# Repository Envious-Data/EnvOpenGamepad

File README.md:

# EnvOpenGamepad
 An open source gamepad using a RP2040 designed to be like popular gamepads but with a few bonus features and ease of repairability.

## Planned features
- layout similar to popular models
- additional buttons over popular models
- turbo mode
- hall effect sticks and triggers

## Features I want but cant implement (yet?)
- vibration/rumble
- wireless
- touchpad?

## Why

no real reason, I had this idea bouncing around in my head for ages so to procrastinate on other projects ill work on this one till I procrastinate on this one by working on others but really I just enjoy designing and making things and if they serve as a good example to do something whilst also helping me learn then its doing one of its main jobs.

I generally like things that can be repaired so if I can make something that surpasses a commercially avaliable example while being reasonable in cost then thats great because I really dont like not being able to repair things which is sometimes the case for commercially avaliable solutions.

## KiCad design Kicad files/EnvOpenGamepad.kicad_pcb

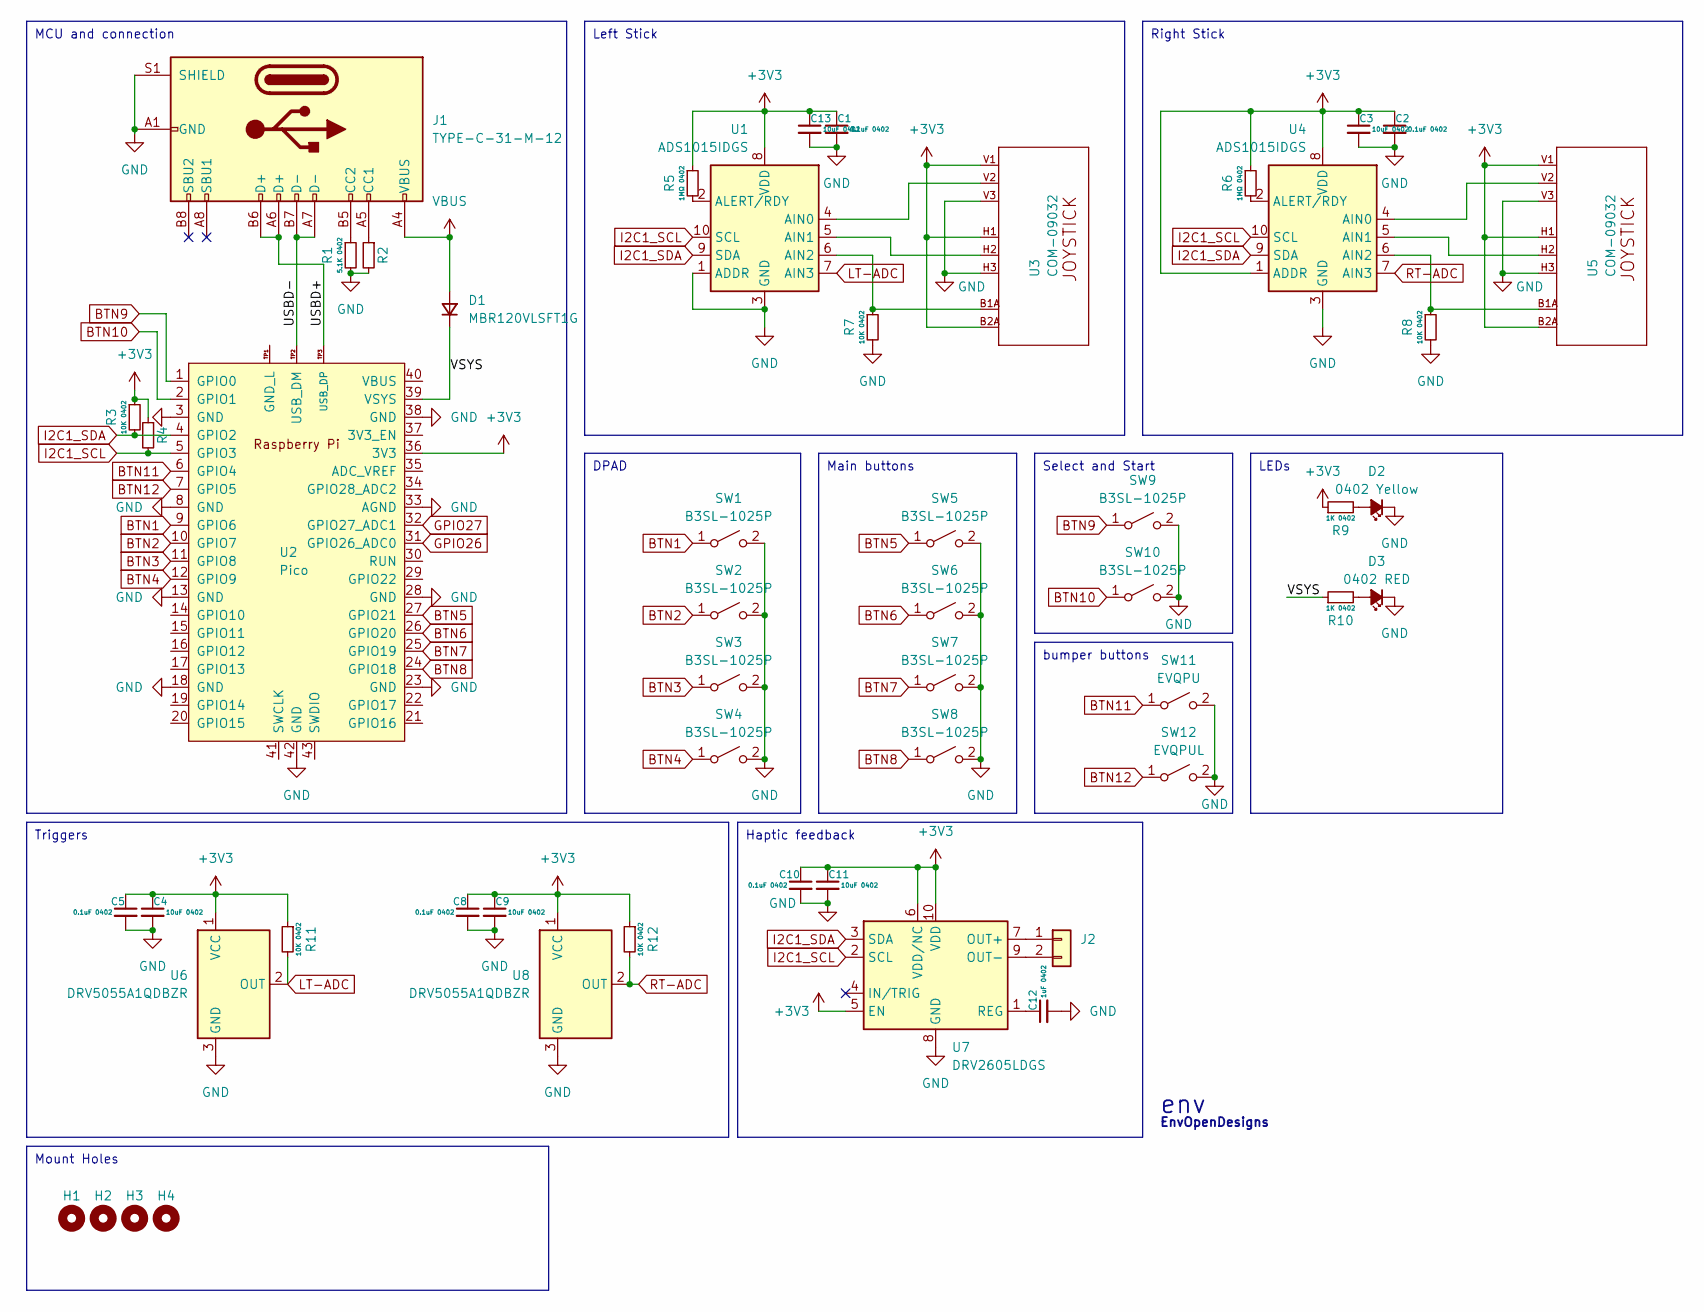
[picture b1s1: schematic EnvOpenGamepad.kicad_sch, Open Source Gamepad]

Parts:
C1, C2, C5, C8, C10: 0.1uF 0402; C_0402_1005Metric
C3, C4, C9, C11, C13: 10uF 0402; C_0402_1005Metric
C12: 1uF 0402; C_0402_1005Metric
D1: MBR120VLSFT1G; D_SOD-123F
D2: 0402 Yellow; LED_0402_1005Metric
D3: 0402 RED; LED_0402_1005Metric
H1, H2, H3, H4: M2 Mounting Hole; MountingHole_2.2mm_M2
J1: TYPE-C-31-M-12; USB_C_Receptacle_HRO_TYPE-C-31-M-12
J2: 01x02 2.54mm pin header; PinHeader_1x02_P2.54mm_Vertical
R1, R2, R4: 5.1K 0402; R_0402_1005Metric
R3, R7, R8, R11, R12: 10K 0402; R_0402_1005Metric
R5, R6: 1MΩ 0402; R_0402_1005Metric
R9, R10: 1K 0402; R_0402_1005Metric
SW1, SW2, SW3, SW4, SW5, SW6, SW7, SW8, SW9, SW10: B3SL-1025P; SW_SPST_B3SL-1022P
SW11: EVQPU; Panasonic_EVQPUL_EVQPUC
SW12: EVQPUL; Panasonic_EVQPUL_EVQPUC
U1, U4: ADS1015IDGS; TSSOP-10_3x3mm_P0.5mm
U2: Pico; RPi_Pico_SMD_TH
U3, U5: COM-09032; JOYSTICK
U6, U8: DRV5055A1QDBZR; SOT-23
U7: DRV2605LDGS; VSSOP-10_3x3mm_P0.5mm

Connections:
+3V3: C1.1, C2.1, C3.1, C4.1, C5.1, C8.1, C9.1, C10.1, C11.1, C13.1, R3.1, R4.1, R5.1, R6.1, R9.1, R11.1, R12.1, U1.8 (VDD), U2.36 (3V3), U3.B2A (SEL-), U3.H1 (H+), U3.V1 (V+), U4.1 (ADDR), U4.8 (VDD), U5.B2A (SEL-), U5.H1 (H+), U5.V1 (V+), U6.1 (VCC), U7.5 (EN), U7.6 (VDD/NC), U7.10 (VDD), U8.1 (VCC)
/USBD+: J1.A6 (D+), J1.B6 (D+), U2.TP3 (USB_DP)
/USBD-: J1.A7 (D-), J1.B7 (D-), U2.TP2 (USB_DM)
/VSYS: D1.1 (K), R10.1, U2.39 (VSYS)
BTN1: SW1.1 (A), U2.9 (GPIO6)
BTN2: SW2.1 (A), U2.10 (GPIO7)
BTN3: SW3.1 (A), U2.11 (GPIO8)
BTN4: SW4.1 (A), U2.12 (GPIO9)
BTN5: SW5.1 (A), U2.27 (GPIO21)
BTN6: SW6.1 (A), U2.26 (GPIO20)
BTN7: SW7.1 (A), U2.25 (GPIO19)
BTN8: SW8.1 (A), U2.24 (GPIO18)
BTN9: SW9.1 (A), U2.1 (GPIO0)
BTN10: SW10.1 (A), U2.2 (GPIO1)
BTN11: SW11.1 (A), U2.6 (GPIO4)
BTN12: SW12.1 (A), U2.7 (GPIO5)
GND: C1.2, C2.2, C3.2, C4.2, C5.2, C8.2, C9.2, C10.2, C11.2, C12.2, C13.2, D2.1 (K), D3.1 (K), J1.A1 (GND), J1.A12 (GND), J1.B1 (GND), J1.B12 (GND), J1.S1 (SHIELD), R1.2, R2.2, R7.2, R8.2, SW1.2 (B), SW2.2 (B), SW3.2 (B), SW4.2 (B), SW5.2 (B), SW6.2 (B), SW7.2 (B), SW8.2 (B), SW9.2 (B), SW10.2 (B), SW11.2 (B), SW12.2 (B), U1.1 (ADDR), U1.3 (GND), U2.3 (GND), U2.8 (GND), U2.13 (GND), U2.18 (GND), U2.23 (GND), U2.28 (GND), U2.33 (AGND), U2.38 (GND), U2.42 (GND), U3.H3 (H-), U3.V3 (V-), U4.3 (GND), U5.H3 (H-), U5.V3 (V-), U6.3 (GND), U7.8 (GND), U8.3 (GND)
GPIO26: U2.31 (GPIO26_ADC0)
GPIO27: U2.32 (GPIO27_ADC1)
I2C1_SCL: R4.2, U1.10 (SCL), U2.5 (GPIO3), U4.10 (SCL), U7.2 (SCL)
I2C1_SDA: R3.2, U1.9 (SDA), U2.4 (GPIO2), U4.9 (SDA), U7.3 (SDA)
LT-ADC: R11.2, U1.7 (AIN3), U6.2 (OUT)
unnamed: D2.2 (A), R9.2
unnamed: D3.2 (A), R10.2
unnamed: J1.A5 (CC1), R2.1
unnamed: J1.B5 (CC2), R1.1
unnamed: J2.1, U7.7 (OUT+)
unnamed: J2.2, U7.9 (OUT-)
unnamed: U1.4 (AIN0), U3.V2 (V)
unnamed: U1.5 (AIN1), U3.H2 (H)
unnamed: R7.1, U1.6 (AIN2), U3.B1A (SEL+)
unnamed: R5.2, U1.2 (ALERT/RDY)
unnamed: U4.4 (AIN0), U5.V2 (V)
unnamed: U4.5 (AIN1), U5.H2 (H)
unnamed: R8.1, U4.6 (AIN2), U5.B1A (SEL+)
unnamed: R6.2, U4.2 (ALERT/RDY)
unnamed: C12.1, U7.1 (REG)
RT-ADC: R12.2, U4.7 (AIN3), U8.2 (OUT)
VBUS: D1.2 (A), J1.A4 (VBUS), J1.A9 (VBUS), J1.B4 (VBUS), J1.B9 (VBUS)

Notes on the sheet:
Main buttons
MCU and connection
bumper buttons
Triggers
Mount Holes
Left Stick
Haptic feedback
Right Stick
Select and Start
LEDs
DPAD
env
EnvOpenDesigns

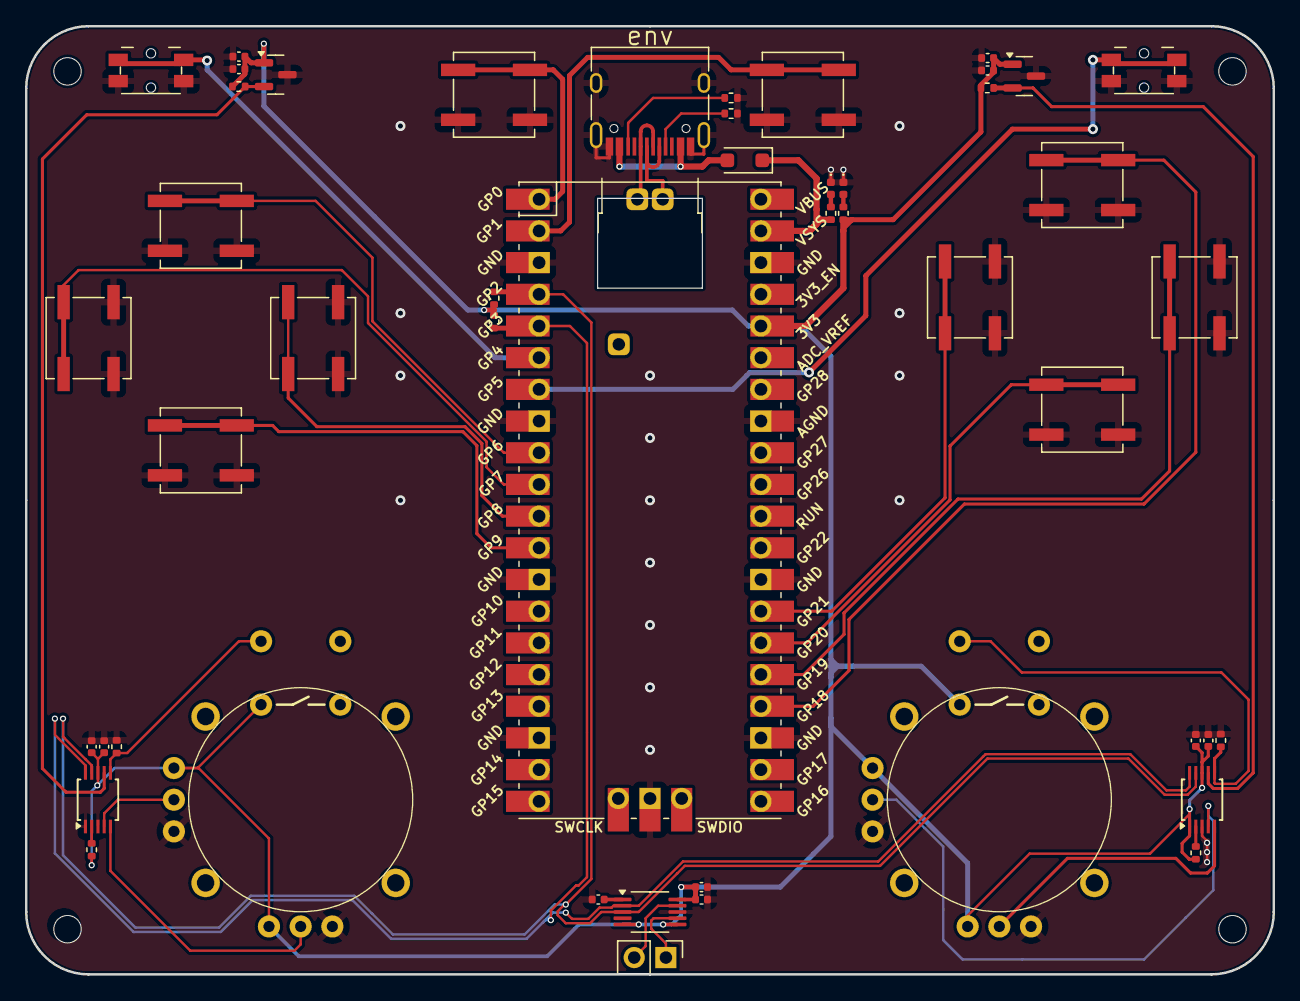
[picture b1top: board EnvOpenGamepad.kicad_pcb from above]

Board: 2 copper layers, 100.0 x 76.0 mm, 52 parts (0 on the bottom side), 37 nets.

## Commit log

2024-09-23 completed schematic and started work on PCB
2024-09-23 Create LICENSE
2025-02-04 updated schematic and completed pcb wiring, generated pcb production files.
2025-03-02 unsure of current changes
